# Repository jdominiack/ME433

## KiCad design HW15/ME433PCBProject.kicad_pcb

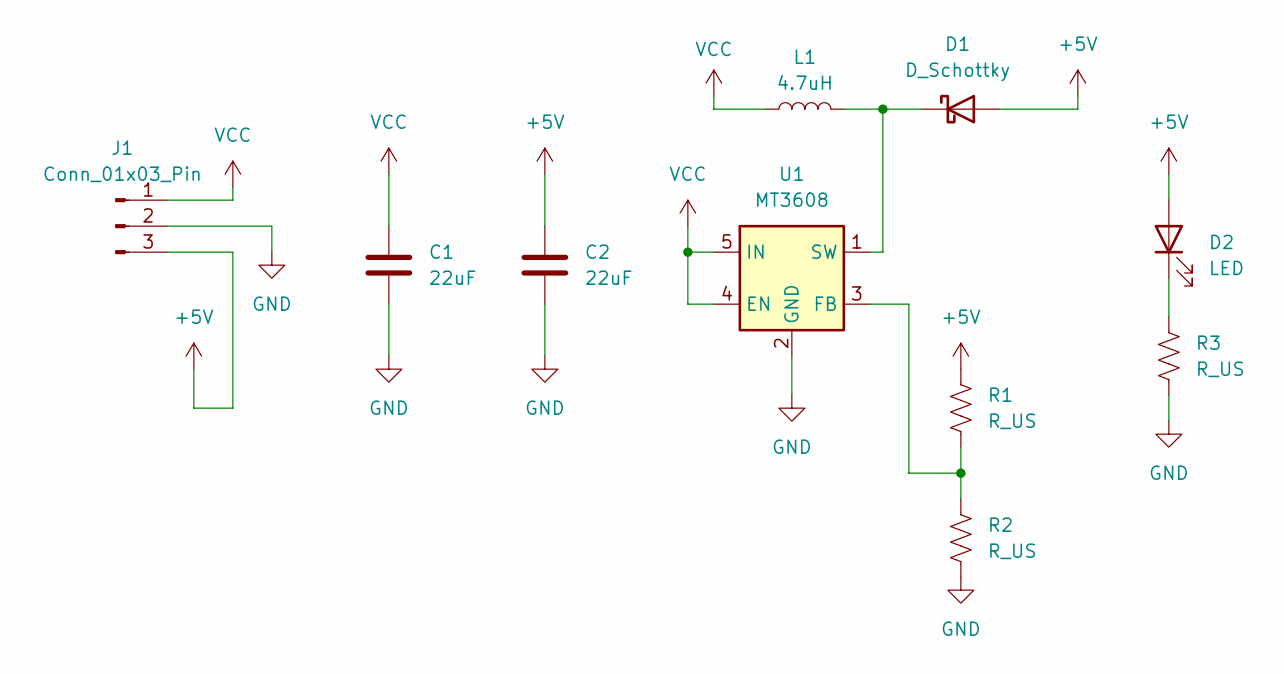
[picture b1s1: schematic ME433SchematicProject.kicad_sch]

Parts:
C1, C2: 22uF; C_0805_2012Metric
D1: D_Schottky; D_SOD-123
D2: LED; LED_D3.0mm
J1: Conn_01x03_Pin; PinSocket_1x03_P2.54mm_Vertical
L1: 4.7uH; L_0402_1005Metric
R1, R2, R3: R_US; R_0805_2012Metric_Pad1.20x1.40mm_HandSolder
U1: MT3608; SOT-23-6

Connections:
+5V: C2.1, D1.2 (A), D2.2 (A), J1.3, R1.1
GND: C1.2, C2.2, J1.2, R2.2, R3.2, U1.2 (GND)
unnamed: D1.1 (K), L1.2, U1.1 (SW)
unnamed: D2.1 (K), R3.1
unnamed: R1.2, R2.1, U1.3 (FB)
VCC: C1.1, J1.1, L1.1, U1.4 (EN), U1.5 (IN)

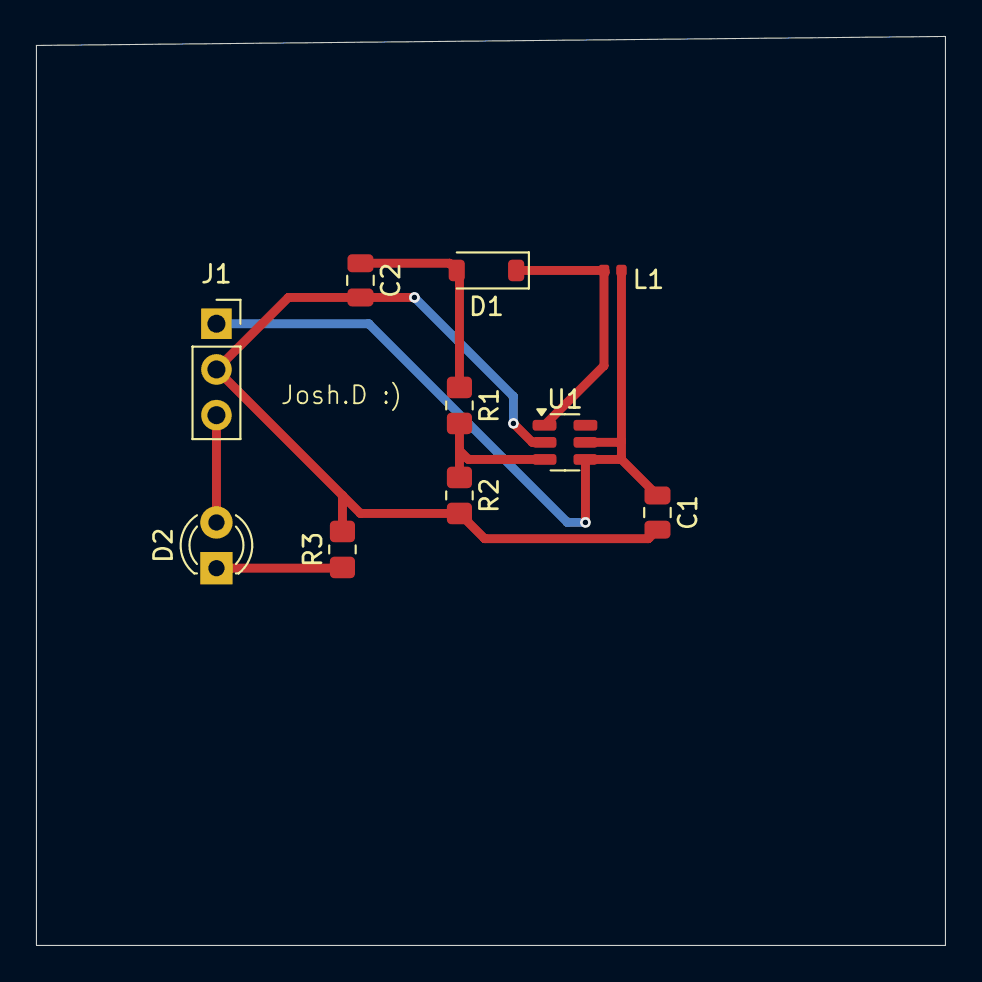
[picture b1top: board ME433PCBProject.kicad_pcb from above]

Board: 2 copper layers, 50.5 x 50.5 mm, 10 parts (0 on the bottom side), 6 nets.

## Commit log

2025-04-08 Completed HW2
2025-05-04 HW3 Final
2025-05-04 HW4 Draft
2025-05-11 HW4 Complete
2025-05-16 HW5 Draft
2025-05-17 HW6 Draft
2025-05-17 HW5/6 Final
2025-05-17 HW7 Start
2025-05-18 HW7 Final
2025-05-18 HW8 Draft
2025-05-19 HW4 Images
2025-05-19 HW5 Picture
2025-05-19 HW9 Final
2025-05-25 HW10
2025-05-26 HW11
2025-05-30 HW13 Final
2025-06-02 HW15
2025-06-02 HW16 Draft
2025-06-03 HW16 Final
2025-06-04 HW14
2025-06-05 HW12
